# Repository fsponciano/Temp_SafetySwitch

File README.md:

# Temperature-controlled safety switch
Francisco S. Ponciano Ojeda
Superradiant Laser Lab, FEMTO-ST, 2021
---

Design of hardware & software for implementation of a temperature-controlled safety switch for use in research laboratories.
The design was carried out with straight-forward considerations that would allow for the desired operation:
- Low-noise voltage supply to avoid affecting measurement noise.
- Output to allow for safe shutdown of critical power supplies that could generate run-away heating.
- Interface with existing temperature monitoring setup (type K thermocouples) in our experiment.
- User-defined set-points for each input channel.
- External reset button for avoiding accidental reactivation of power supplies.
- Small footprint to allow for switch to be easily incorporated into any space limitations.

As we want to have good precision (<10mV) in the reading of analog signals, we have opted to use the (Teensy 4.0 microcontroller)[http://] and the `ADC` library.
This allows for the analog inputs to be configured to read with 12-bit resolution (~800µV) with some averaging that takes advantage of the speed of the Teensy's speed.

---

The repository contains the KiCAD project with the circuit schematics + PCB designs for construction of this switch.
**Note:** The hardware is split into two PCBs: one for the signal inputs (*i.e.* the thermocouples) and one for the power input and outpus (*i.e.* the signal relays).

A BOM is also provided for ease of access to the part numbers of the electronic components used.

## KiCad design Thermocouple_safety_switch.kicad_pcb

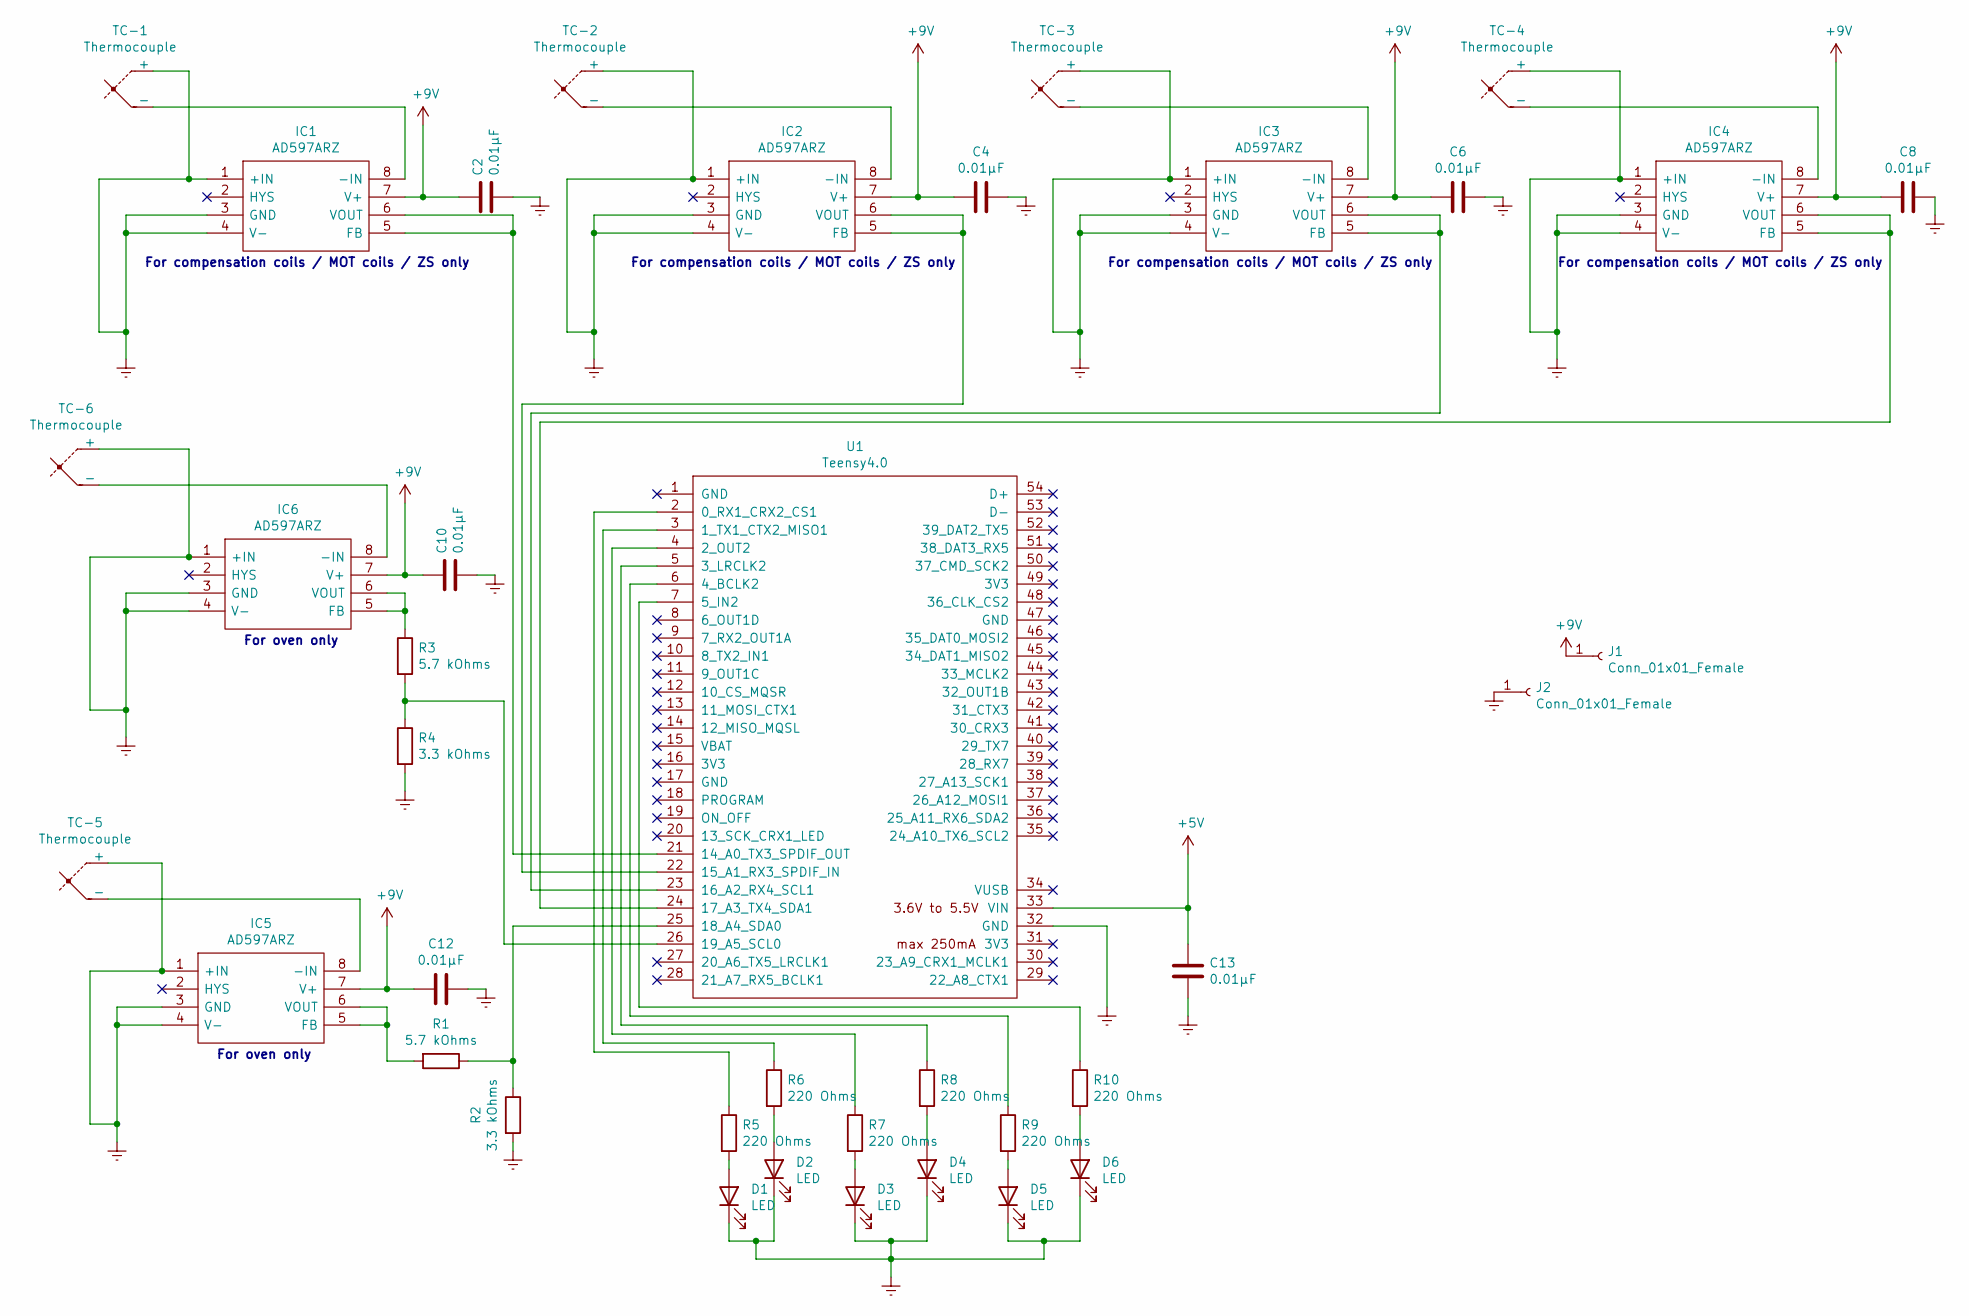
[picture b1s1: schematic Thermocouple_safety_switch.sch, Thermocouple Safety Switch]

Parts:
C2, C4, C6, C8, C10, C12, C13: 0.01µF; C_0805_2012Metric
D1, D2, D3, D4, D5, D6: LED; LED_D3.0mm
IC1, IC2, IC3, IC4, IC5, IC6: AD597ARZ; SOIC127P600X175-8N; Manufacturer_Part_Number AD597ARZ; Mouser Part Number 584-AD597ARZ
J1, J2: Conn_01x01_Female; SolderWire-2sqmm_1x01_D2mm_OD3.9mm
R1, R3: 5.7 kOhms; R_Axial_DIN0207_L6.3mm_D2.5mm_P10.16mm_Horizontal
R2, R4: 3.3 kOhms; R_Axial_DIN0207_L6.3mm_D2.5mm_P10.16mm_Horizontal
R5, R6, R7, R8, R9, R10: 220 Ohms; R_Axial_DIN0207_L6.3mm_D2.5mm_P10.16mm_Horizontal
TC-1, TC-2, TC-3, TC-4, TC-5, TC-6: Thermocouple; SolderWire-1sqmm_1x02_P5.4mm_D1.4mm_OD2.7mm
U1: Teensy4.0; Teensy40_SMT

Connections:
+5V: C13.1, U1.33 (VIN)
+9V: C2.1, C4.1, C6.1, C8.2, C10.1, C12.1, IC1.7 (V+), IC2.7 (V+), IC3.7 (V+), IC4.7 (V+), IC5.7 (V+), IC6.7 (V+), J1.1
Earth: C2.2, C4.2, C6.2, C8.1, C10.2, C12.2, C13.2, D1.1 (K), D2.1 (K), D3.1 (K), D4.1 (K), D5.1 (K), D6.1 (K), IC1.1 (+IN), IC1.3 (GND), IC1.4 (V-), IC2.1 (+IN), IC2.3 (GND), IC2.4 (V-), IC3.1 (+IN), IC3.3 (GND), IC3.4 (V-), IC4.1 (+IN), IC4.3 (GND), IC4.4 (V-), IC5.1 (+IN), IC5.3 (GND), IC5.4 (V-), IC6.1 (+IN), IC6.3 (GND), IC6.4 (V-), J2.1, R2.2, R4.2, TC-1.1 (+), TC-2.1 (+), TC-3.1 (+), TC-4.1 (+), TC-5.1 (+), TC-6.1 (+), U1.32 (GND)
unnamed: D1.2 (A), R5.2
unnamed: D2.2 (A), R6.2
unnamed: D3.2 (A), R7.2
unnamed: D4.2 (A), R8.2
unnamed: D5.2 (A), R9.2
unnamed: D6.2 (A), R10.2
unnamed: IC1.5 (FB), IC1.6 (VOUT), U1.21 (14_A0_TX3_SPDIF_OUT)
unnamed: IC1.8 (-IN), TC-1.2 (-)
unnamed: IC2.5 (FB), IC2.6 (VOUT), U1.22 (15_A1_RX3_SPDIF_IN)
unnamed: IC2.8 (-IN), TC-2.2 (-)
unnamed: IC3.5 (FB), IC3.6 (VOUT), U1.23 (16_A2_RX4_SCL1)
unnamed: IC3.8 (-IN), TC-3.2 (-)
unnamed: IC4.5 (FB), IC4.6 (VOUT), U1.24 (17_A3_TX4_SDA1)
unnamed: IC4.8 (-IN), TC-4.2 (-)
unnamed: IC5.5 (FB), IC5.6 (VOUT), R1.2
unnamed: IC5.8 (-IN), TC-5.2 (-)
unnamed: IC6.5 (FB), IC6.6 (VOUT), R3.1
unnamed: IC6.8 (-IN), TC-6.2 (-)
unnamed: R1.1, R2.1, U1.25 (18_A4_SDA0)
unnamed: R3.2, R4.1, U1.26 (19_A5_SCL0)
unnamed: R5.1, U1.2 (0_RX1_CRX2_CS1)
unnamed: R6.1, U1.3 (1_TX1_CTX2_MISO1)
unnamed: R7.1, U1.4 (2_OUT2)
unnamed: R8.1, U1.5 (3_LRCLK2)
unnamed: R9.1, U1.6 (4_BCLK2)
unnamed: R10.1, U1.7 (5_IN2)

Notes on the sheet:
For compensation coils / MOT coils / ZS only
For oven only

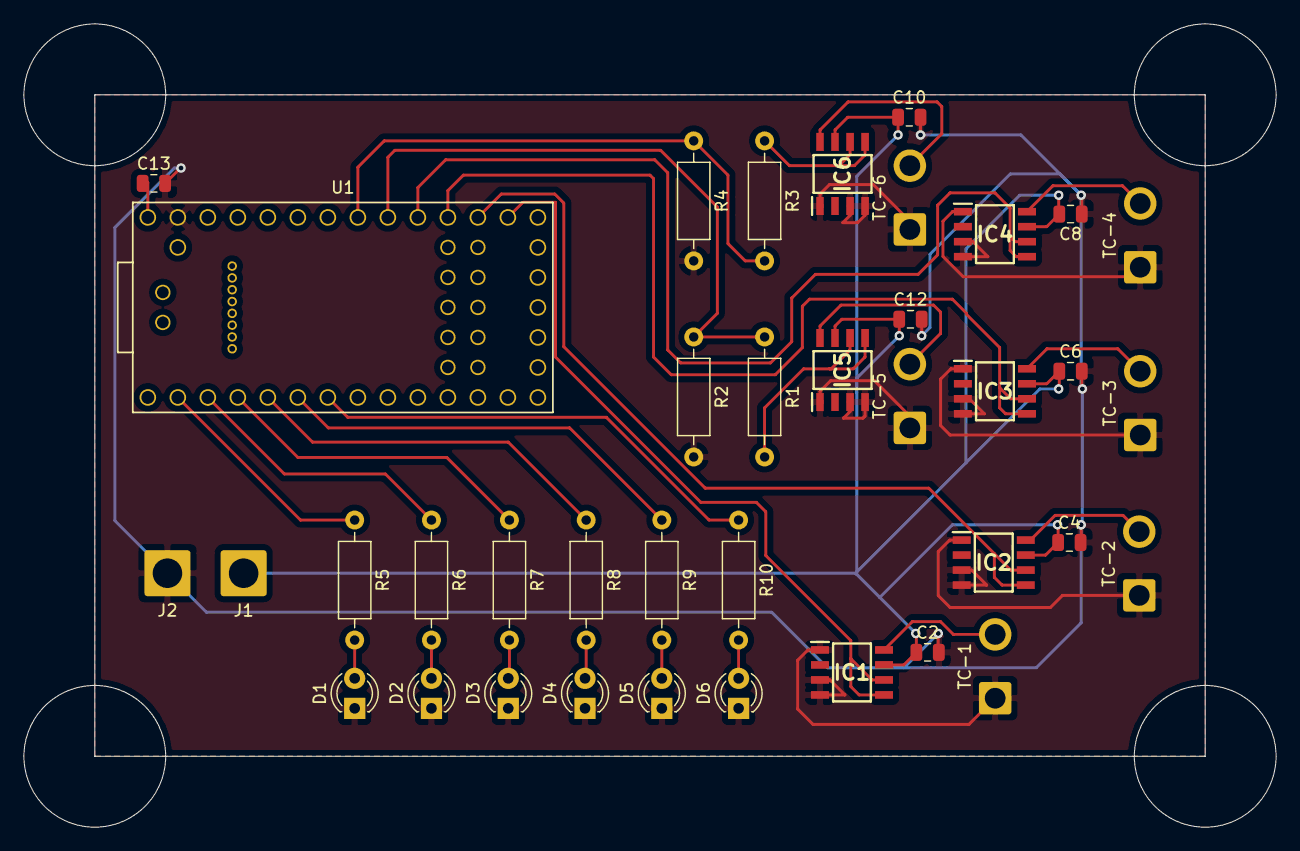
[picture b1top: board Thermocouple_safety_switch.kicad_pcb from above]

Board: 2 copper layers, 106.0 x 68.0 mm, 38 parts (0 on the bottom side), 29 nets.

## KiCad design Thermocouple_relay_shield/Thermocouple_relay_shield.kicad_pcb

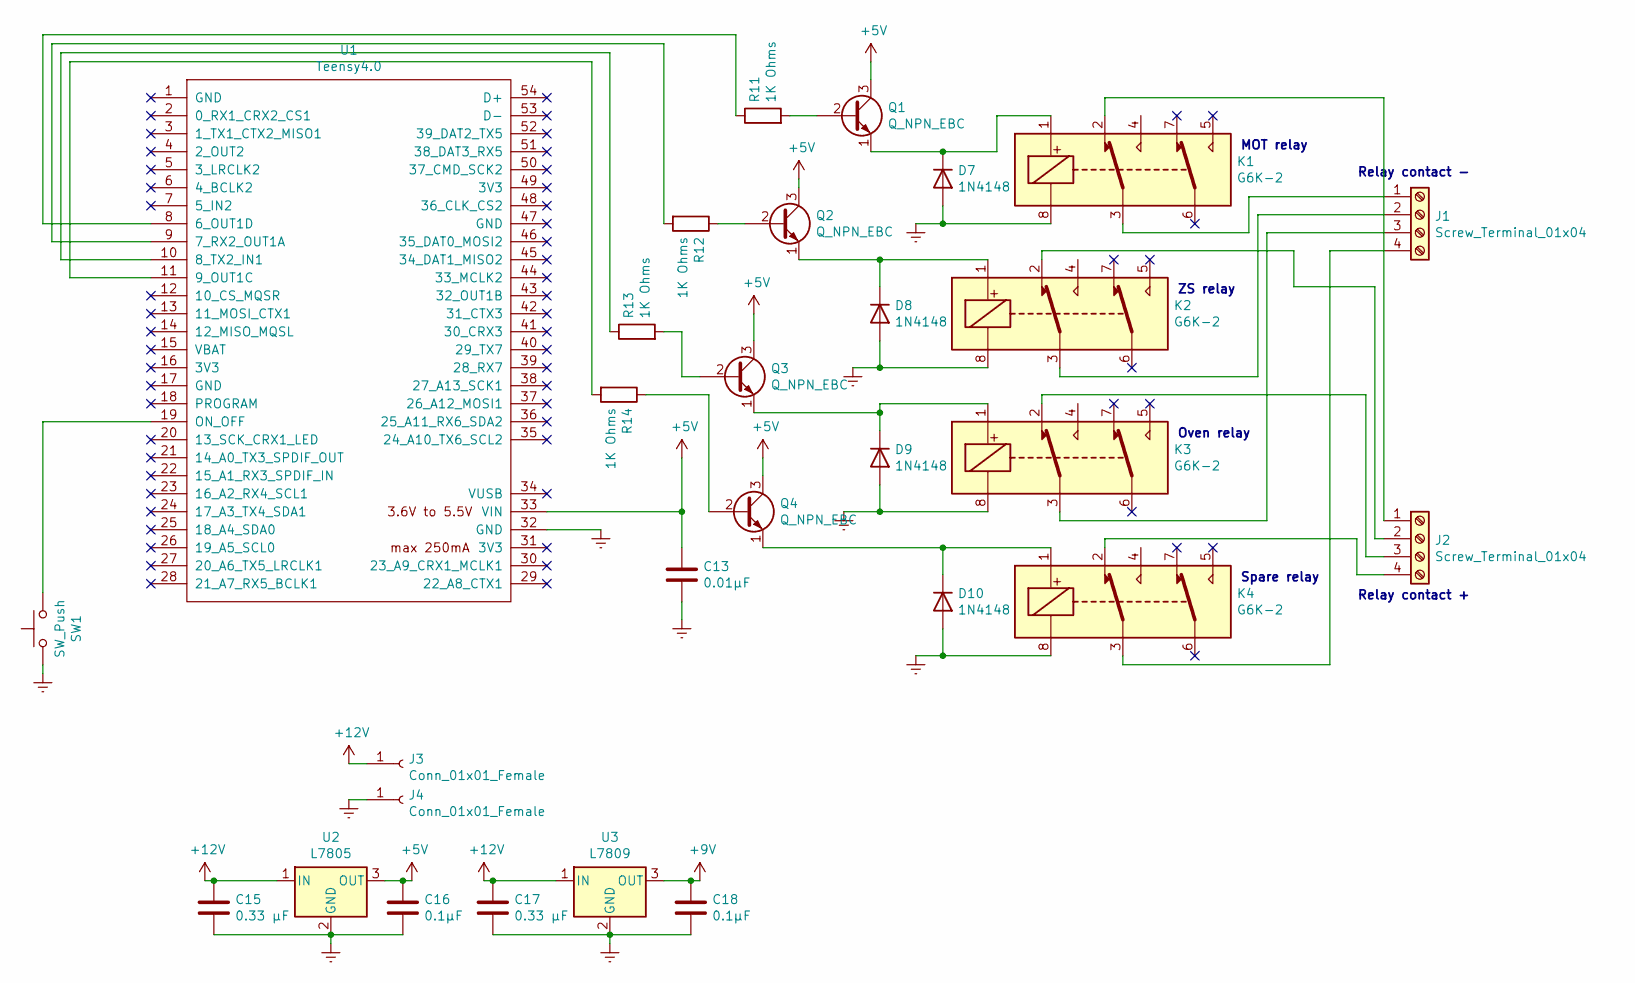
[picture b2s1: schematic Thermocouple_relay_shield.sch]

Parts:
C13: 0.01µF; C_0805_2012Metric
C15, C17: 0.33 µF; C_0805_2012Metric
C16, C18: 0.1µF; C_0805_2012Metric
D7, D8, D9, D10: 1N4148; D_DO-35_SOD27_P7.62mm_Horizontal
J1, J2: Screw_Terminal_01x04; TerminalBlock_MetzConnect_Type059_RT06304HBWC_1x04_P3.50mm_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
J3, J4: Conn_01x01_Female; SolderWire-2sqmm_1x01_D2mm_OD3.9mm
K1, K2, K3, K4: G6K-2; Relay_DPDT_Omron_G6K-2F-Y
Q1, Q2, Q3, Q4: Q_NPN_EBC; TO-18-3
R11, R12, R13, R14: 1K Ohms; R_Axial_DIN0207_L6.3mm_D2.5mm_P10.16mm_Horizontal
SW1: SW_Push; SolderWire-1sqmm_1x02_P5.4mm_D1.4mm_OD2.7mm
U1: Teensy4.0; Teensy40_SMT
U2: L7805; TO-220-3_Vertical
U3: L7809; TO-220-3_Vertical

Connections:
+5V: C13.1, C16.1, Q1.3 (C), Q2.3 (C), Q3.3 (C), Q4.3 (C), U1.33 (VIN), U2.3 (OUT)
+9V: C18.1, U3.3 (OUT)
+12V: C15.1, C17.1, J3.1, U2.1 (IN), U3.1 (IN)
Earth: C13.2, C15.2, C16.2, C17.2, C18.2, D7.2 (A), D8.2 (A), D9.2 (A), D10.2 (A), J4.1, K1.8, K2.8, K3.8, K4.8, SW1.1, U1.32 (GND), U2.2 (GND), U3.2 (GND)
unnamed: D7.1 (K), K1.1, Q1.1 (E)
unnamed: D8.1 (K), K2.1, Q2.1 (E)
unnamed: D9.1 (K), K3.1, Q3.1 (E)
unnamed: D10.1 (K), K4.1, Q4.1 (E)
unnamed: J1.1, K1.3
unnamed: J1.2, K2.3
unnamed: J1.3, K3.3
unnamed: J1.4, K4.3
unnamed: J2.1, K1.2
unnamed: J2.2, K2.2
unnamed: J2.3, K3.2
unnamed: J2.4, K4.2
unnamed: Q1.2 (B), R11.2
unnamed: Q2.2 (B), R12.1
unnamed: Q3.2 (B), R13.2
unnamed: Q4.2 (B), R14.1
unnamed: R11.1, U1.8 (6_OUT1D)
unnamed: R12.2, U1.9 (7_RX2_OUT1A)
unnamed: R13.1, U1.10 (8_TX2_IN1)
unnamed: R14.2, U1.11 (9_OUT1C)
unnamed: SW1.2, U1.19 (ON_OFF)

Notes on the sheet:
MOT relay
ZS relay
Oven relay
Spare relay
Relay contact -
Relay contact +

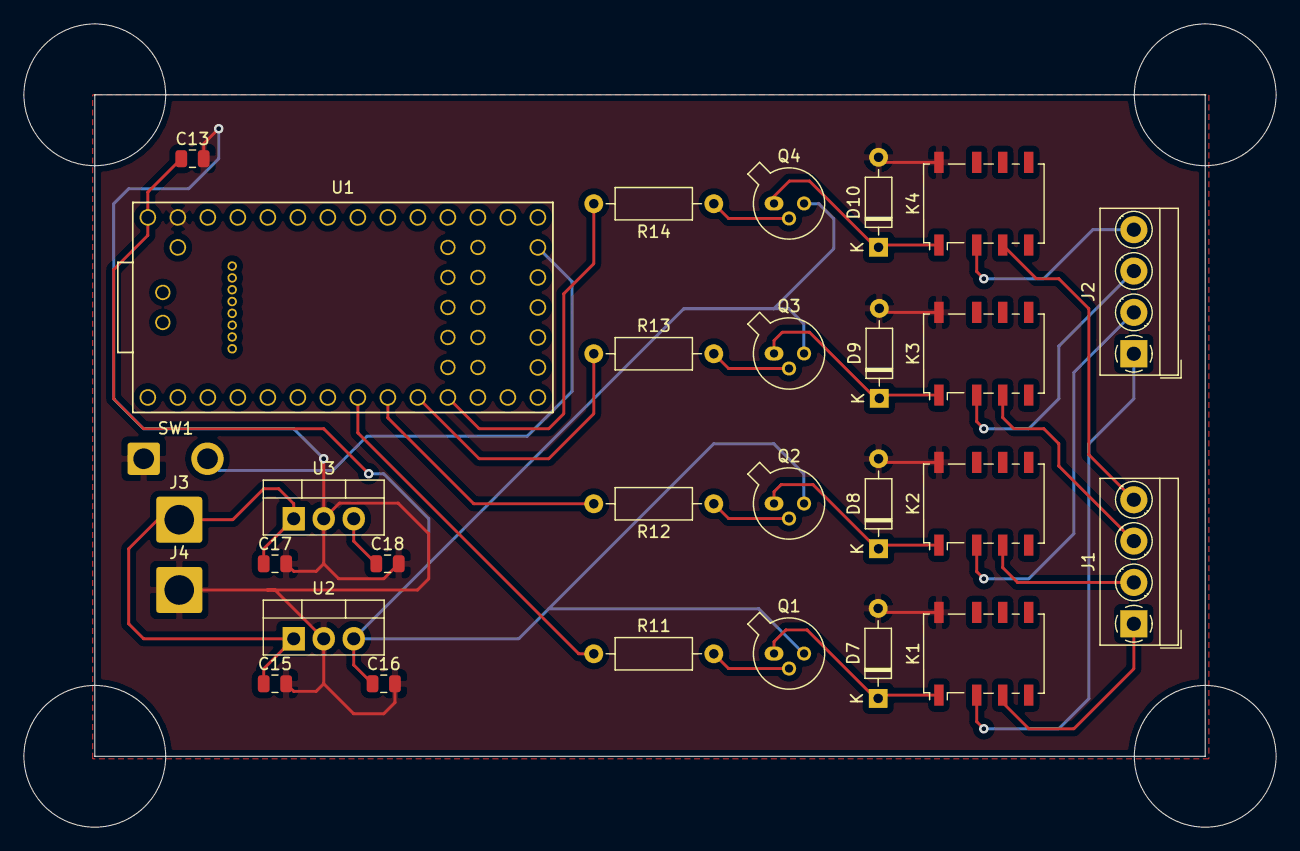
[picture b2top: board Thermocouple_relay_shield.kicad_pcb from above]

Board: 2 copper layers, 106.0 x 68.0 mm, 29 parts (0 on the bottom side), 25 nets.

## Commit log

2021-12-03 Initial upload.
